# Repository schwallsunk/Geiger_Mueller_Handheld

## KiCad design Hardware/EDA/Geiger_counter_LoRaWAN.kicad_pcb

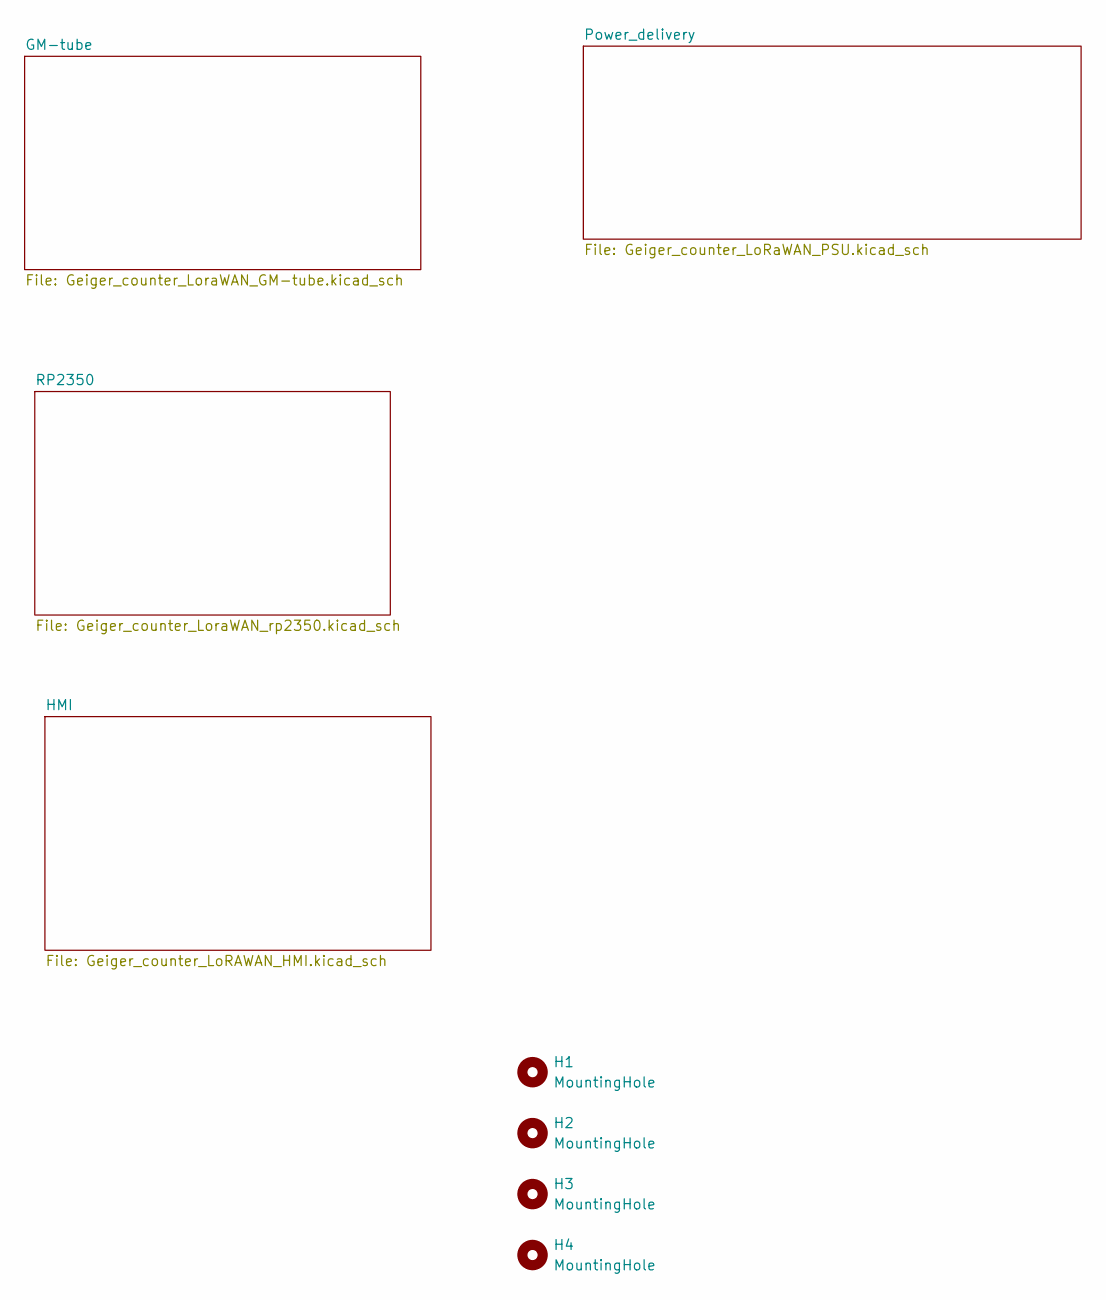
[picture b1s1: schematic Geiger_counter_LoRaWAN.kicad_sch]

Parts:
H1, H2, H3, H4: MountingHole; MountingHole_3.2mm_M3_ISO14580

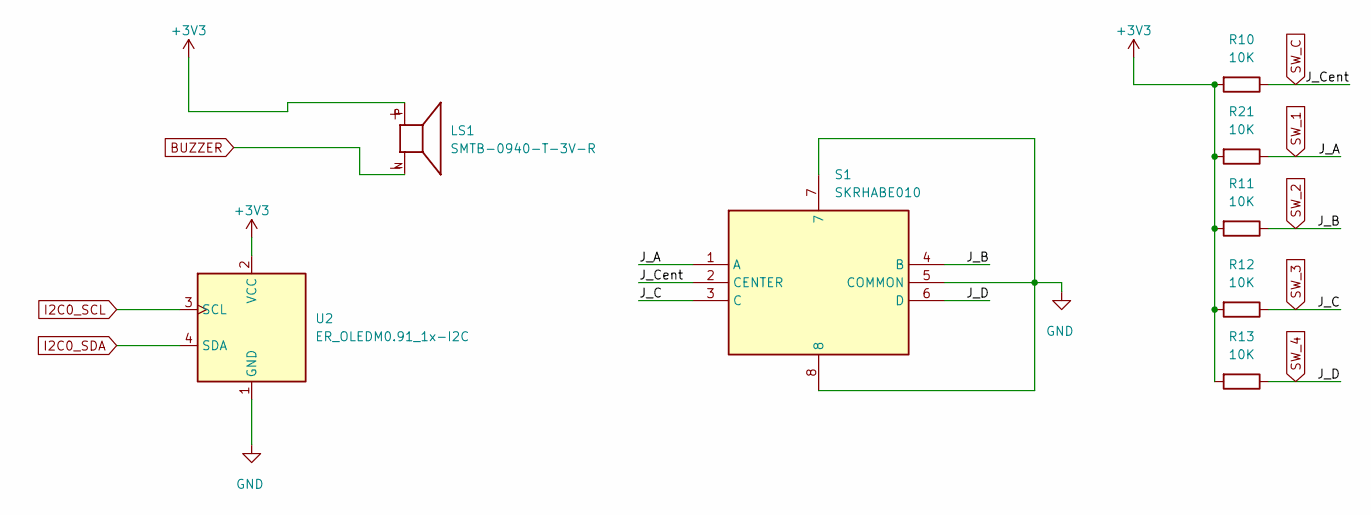
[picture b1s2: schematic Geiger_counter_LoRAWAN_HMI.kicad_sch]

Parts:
LS1: SMTB-0940-T-3V-R; XDCR_SMTB-0940-T-3V-R; PARTREV 01/24/2017
R10, R11, R12, R13, R21: 10K; R_0402_1005Metric
S1: SKRHABE010; Manufacturer_Part_Number SKRHABE010; Mouser Part Number 688-SKRHAB
U2: ER_OLEDM0.91_1x-I2C

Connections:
+3V3: LS1.P, R10.2, R11.2, R12.2, R13.2, R21.2, U2.2 (VCC); also elsewhere on the board
BUZZER: LS1.N; also elsewhere on the board
GND: S1.5 (COMMON), S1.7, S1.8, U2.1 (GND); also elsewhere on the board
I2C0_SCL: U2.3 (SCL); also elsewhere on the board
I2C0_SDA: U2.4 (SDA); also elsewhere on the board
SW_1: R21.1, S1.1 (A); also elsewhere on the board
SW_2: R11.1, S1.4 (B); also elsewhere on the board
SW_3: R12.1, S1.3 (C); also elsewhere on the board
SW_4: R13.1, S1.6 (D); also elsewhere on the board
SW_C: R10.1, S1.2 (CENTER); also elsewhere on the board

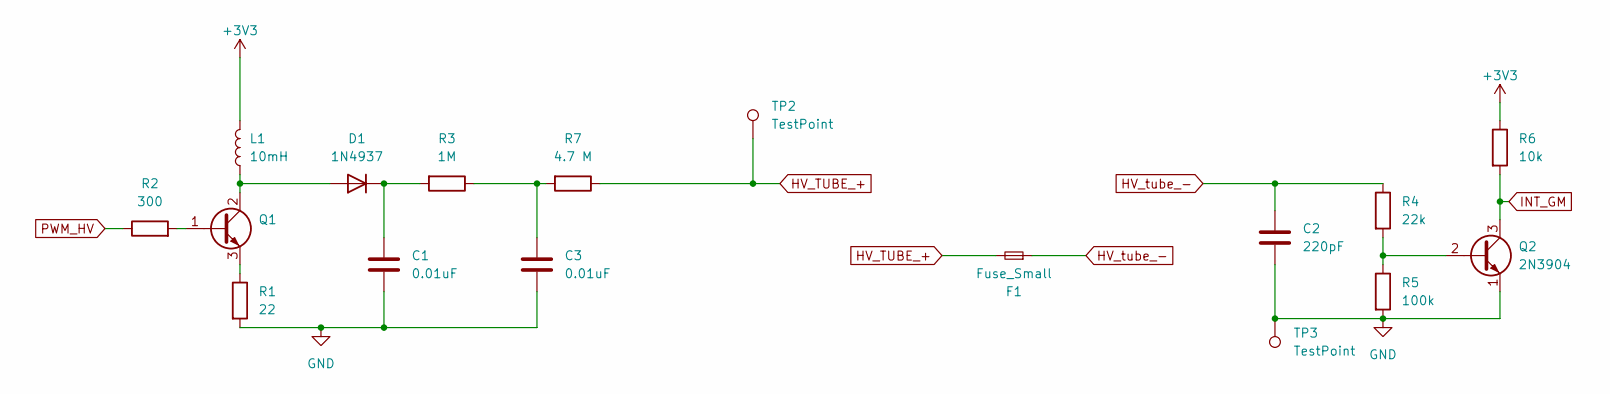
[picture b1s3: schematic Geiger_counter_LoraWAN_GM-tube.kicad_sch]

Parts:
C1, C3: 0.01uF; C_Rect_L11.0mm_W6.3mm_P10.00mm_MKT
C2: 220pF; C_Rect_L16.5mm_W7.3mm_P15.00mm_MKT
D1: 1N4937; D_DO-41_SOD81_P10.16mm_Horizontal
F1: Fuse_Small; SBM-20_GM_holder
L1: 10mH; L_Radial_D9.5mm_P5.00mm_Fastron_07HVP
Q1: MJE13003; TO-92_Inline_Wide
Q2: 2N3904; TO-92_Inline_Wide
R1: 22; R_Axial_DIN0516_L15.5mm_D5.0mm_P20.32mm_Horizontal
R2: 300; R_Axial_DIN0207_L6.3mm_D2.5mm_P10.16mm_Horizontal
R3: 1M; R_Axial_DIN0411_L9.9mm_D3.6mm_P15.24mm_Horizontal
R4: 22k; R_Axial_DIN0516_L15.5mm_D5.0mm_P20.32mm_Horizontal
R5: 100k; R_Axial_DIN0414_L11.9mm_D4.5mm_P20.32mm_Horizontal
R6: 10k; R_Axial_DIN0309_L9.0mm_D3.2mm_P15.24mm_Horizontal
R7: 4.7 M; R_Axial_DIN0411_L9.9mm_D3.6mm_P15.24mm_Horizontal
TP2, TP3: TestPoint; TestPoint_Loop_D2.50mm_Drill1.0mm

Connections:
+3V3: L1.2, R6.1; also elsewhere on the board
GND: C1.2, C2.2, C3.2, Q2.1 (E), R1.2, R5.2, TP3.1 (1_1); also elsewhere on the board
HV_TUBE_+: F1.2, R7.1, TP2.1 (1_1)
HV_tube_-: C2.1, F1.1, R4.1
INT_GM: Q2.3 (C), R6.2; also elsewhere on the board
unnamed: C3.1, R3.1, R7.2
unnamed: D1.2 (A), L1.1, Q1.2 (C)
unnamed: C1.1, D1.1 (K), R3.2
unnamed: Q1.1 (B), R2.2
unnamed: Q1.3 (E), R1.1
unnamed: Q2.2 (B), R4.2, R5.1
PWM_HV: R2.1; also elsewhere on the board

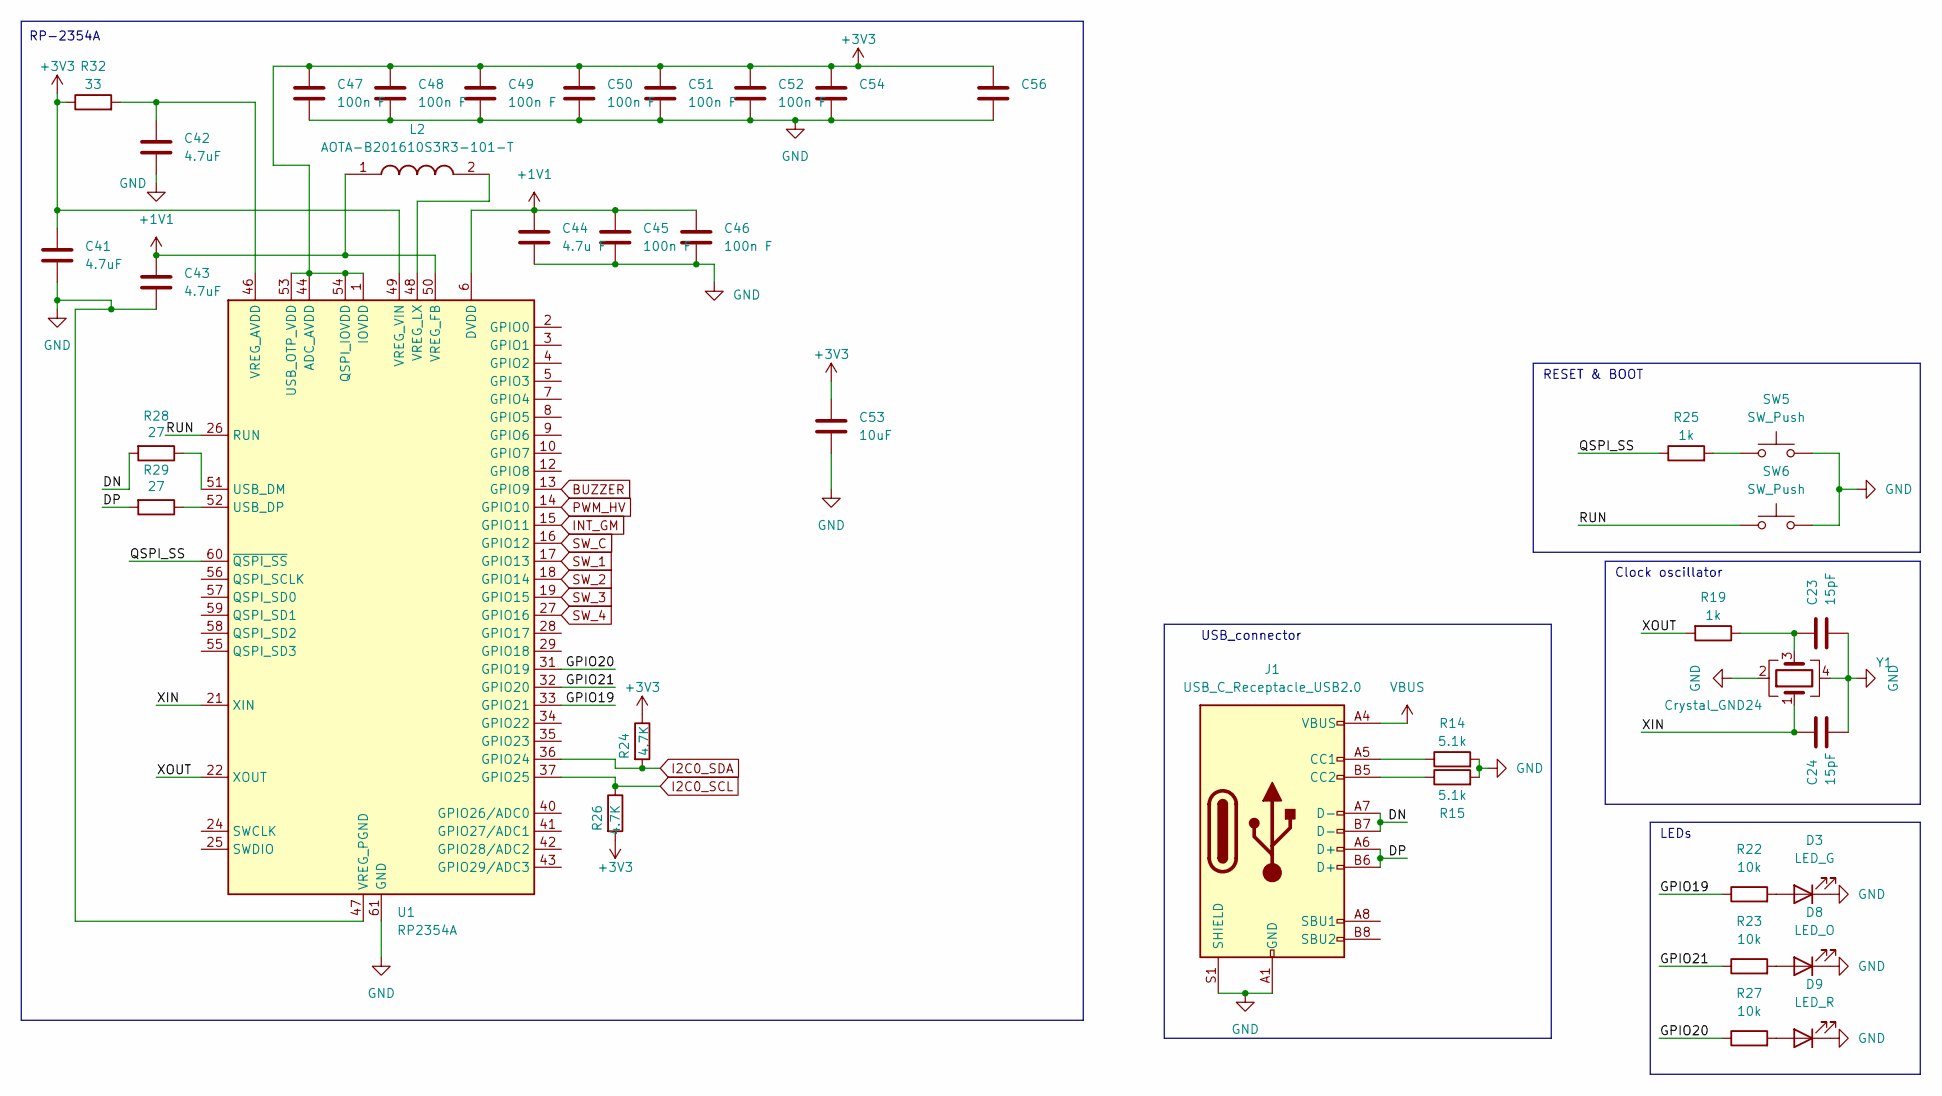
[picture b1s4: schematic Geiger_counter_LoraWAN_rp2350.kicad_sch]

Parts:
C23, C24: 15pF; C_0402_1005Metric_Pad0.74x0.62mm_HandSolder
C41, C42, C43: 4.7uF; C_0402_1005Metric
C44: 4.7u F; C_0402_1005Metric
C45, C46, C47, C48, C49, C50, C51, C52, C54, C56: 100n F; C_0201_0603Metric
C53: 10uF; C_0603_1608Metric
D3: LED_G; LED_0603_1608Metric_Pad1.05x0.95mm_HandSolder
D8: LED_O; LED_0603_1608Metric_Pad1.05x0.95mm_HandSolder
D9: LED_R; LED_0603_1608Metric_Pad1.05x0.95mm_HandSolder
J1: USB_C_Receptacle_USB2.0; USB_C_Receptacle_G-Switch_GT-USB-7010ASV
L2: AOTA-B201610S3R3-101-T; AOTAB201610S3R3101T; Manufacturer_Part_Number AOTA-B201610S3R3-101-T; Mouser Part Number 815-AB201610S3R3101T
R14, R15: 5.1k; R_0402_1005Metric_Pad0.72x0.64mm_HandSolder
R19, R25: 1k; R_0402_1005Metric_Pad0.72x0.64mm_HandSolder
R22, R23, R27: 10k; R_0402_1005Metric
R24, R26: 4.7K; R_0402_1005Metric_Pad0.72x0.64mm_HandSolder
R28, R29: 27; R_0402_1005Metric
R32: 33; R_0402_1005Metric_Pad0.72x0.64mm_HandSolder
SW5, SW6: SW_Push; SW_SPST_CK_RS282G05A3
U1: RP2354A; QFN-60-1EP_7x7mm_P0.4mm_EP3.4x3.4mm
Y1: Crystal_GND24; Crystal_SMD_3225-4Pin_3.2x2.5mm

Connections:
+1V1: C43.1, C44.1, C45.1, C46.1, L2.1, U1.6 (DVDD), U1.23 (DVDD), U1.39 (DVDD), U1.50 (VREG_FB)
+3V3: C41.1, C47.1, C48.1, C49.1, C50.1, C51.1, C52.1, C53.2, C54.1, C56.1, R24.1, R26.2, R32.1, U1.1 (IOVDD), U1.11 (IOVDD), U1.20 (IOVDD), U1.30 (IOVDD), U1.38 (IOVDD), U1.44 (ADC_AVDD), U1.45 (IOVDD), U1.49 (VREG_VIN), U1.53 (USB_OTP_VDD), U1.54 (QSPI_IOVDD); also elsewhere on the board
/RP2350/DN: J1.A7 (D-), J1.B7 (D-), R28.2
/RP2350/DP: J1.A6 (D+), J1.B6 (D+), R29.2
/RP2350/GPIO19: R22.1, U1.33 (GPIO21)
/RP2350/GPIO20: R27.1, U1.31 (GPIO19)
/RP2350/GPIO21: R23.1, U1.32 (GPIO20)
/RP2350/QSPI_SS: R25.1, U1.60 (~QSPI_SS)
/RP2350/RUN: SW6.1, U1.26 (RUN)
/RP2350/XIN: C24.1, U1.21 (XIN), Y1.1
/RP2350/XOUT: R19.2, U1.22 (XOUT)
BUZZER: U1.13 (GPIO9); also elsewhere on the board
GND: C23.2, C24.2, C41.2, C42.2, C43.2, C44.2, C45.2, C46.2, C47.2, C48.2, C49.2, C50.2, C51.2, C52.2, C53.1, C54.2, C56.2, D3.1 (K), D8.1 (K), D9.1 (K), J1.A1 (GND), J1.A12 (GND), J1.B1 (GND), J1.B12 (GND), J1.S1 (SHIELD), R14.2, R15.2, SW5.2, SW6.2, U1.47 (VREG_PGND), U1.61 (GND), Y1.2, Y1.4; also elsewhere on the board
I2C0_SCL: R26.1, U1.37 (GPIO25); also elsewhere on the board
I2C0_SDA: R24.2, U1.36 (GPIO24); also elsewhere on the board
INT_GM: U1.15 (GPIO11); also elsewhere on the board
unnamed: C23.1, R19.1, Y1.3
unnamed: D3.2 (A), R22.2
unnamed: D8.2 (A), R23.2
unnamed: D9.2 (A), R27.2
unnamed: J1.A5 (CC1), R14.1
unnamed: J1.B5 (CC2), R15.1
unnamed: R25.2, SW5.1
unnamed: R28.1, U1.51 (USB_DM)
unnamed: R29.1, U1.52 (USB_DP)
unnamed: C42.1, R32.2, U1.46 (VREG_AVDD)
unnamed: L2.2, U1.48 (VREG_LX)
PWM_HV: U1.14 (GPIO10); also elsewhere on the board
SW_1: U1.17 (GPIO13); also elsewhere on the board
SW_2: U1.18 (GPIO14); also elsewhere on the board
SW_3: U1.19 (GPIO15); also elsewhere on the board
SW_4: U1.27 (GPIO16); also elsewhere on the board
SW_C: U1.16 (GPIO12); also elsewhere on the board
VBUS: J1.A4 (VBUS), J1.A9 (VBUS), J1.B4 (VBUS), J1.B9 (VBUS); also elsewhere on the board

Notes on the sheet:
Clock oscillator
RESET & BOOT
RP-2354A
USB_connector
LEDs

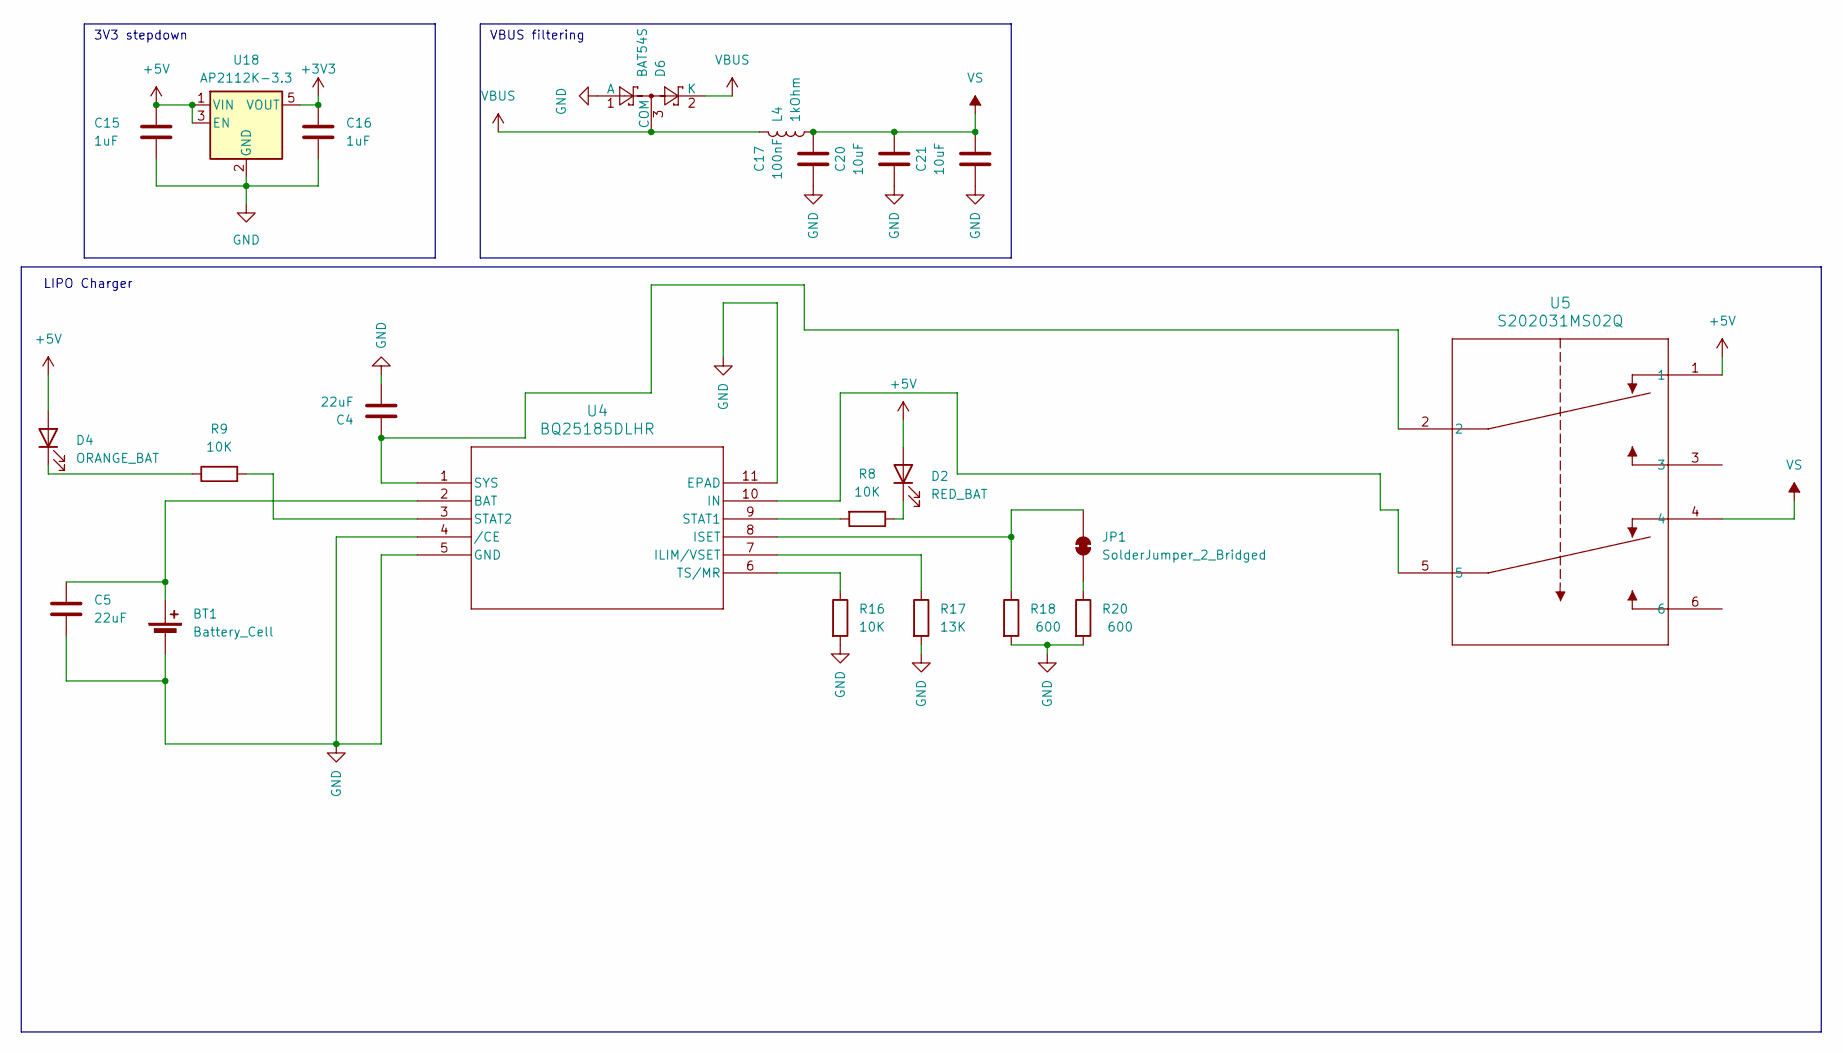
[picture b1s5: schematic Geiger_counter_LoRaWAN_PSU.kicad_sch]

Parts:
BT1: Battery_Cell; BatteryHolder_Keystone_1042_1x18650
C4: 22uF; C_0603_1608Metric
C5: 22uF; C_0402_1005Metric
C15, C16: 1uF; C_0603_1608Metric_Pad1.08x0.95mm_HandSolder
C17: 100nF; R_0603_1608Metric_Pad0.98x0.95mm_HandSolder
C20, C21: 10uF; C_1206_3216Metric_Pad1.33x1.80mm_HandSolder
D2: RED_BAT; LED_0603_1608Metric_Pad1.05x0.95mm_HandSolder
D4: ORANGE_BAT; LED_0603_1608Metric_Pad1.05x0.95mm_HandSolder
D6: BAT54S; SOT-23
JP1: SolderJumper_2_Bridged; SolderJumper-2_P1.3mm_Open_Pad1.0x1.5mm
L4: 1kOhm; R_0603_1608Metric_Pad0.98x0.95mm_HandSolder
R8, R9, R16: 10K; R_0402_1005Metric
R17: 13K; R_0402_1005Metric
R18, R20: 600; R_0402_1005Metric
U4: BQ25185DLHR; WSON10_DLH_TEX-M
U5: S202031MS02Q; SWITCH_S20203
U18: AP2112K-3.3; SOT-23-5

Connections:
+3V3: C16.1, U18.5 (VOUT); also elsewhere on the board
+5V: C15.1, D2.2 (A), D4.2 (A), U5.1, U18.1 (VIN), U18.3 (EN)
GND: BT1.2 (-), C4.2, C5.2, C15.2, C16.2, C17.2, C20.2, C21.1, D6.1 (A), R16.2, R17.2, R18.2, R20.2, U4.4 (/CE), U4.5 (GND), U4.11 (EPAD), U18.2 (GND); also elsewhere on the board
unnamed: BT1.1 (+), C5.1, U4.2 (BAT)
unnamed: D2.1 (K), R8.1
unnamed: D4.1 (K), R9.1
unnamed: JP1.1 (A), R20.1
unnamed: JP1.2 (B), R18.1, U4.8 (ISET)
unnamed: R17.1, U4.7 (ILIM/VSET)
unnamed: U4.10 (IN), U5.5
unnamed: R8.2, U4.9 (STAT1)
unnamed: R9.2, U4.3 (STAT2)
unnamed: C4.1, U4.1 (SYS), U5.2
unnamed: R16.1, U4.6 (TS/MR)
VBUS: D6.2 (K), D6.3 (COM), L4.2; also elsewhere on the board
VS: C17.1, C20.1, C21.2, L4.1, U5.4

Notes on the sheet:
LIPO Charger
VBUS filtering
3V3 stepdown

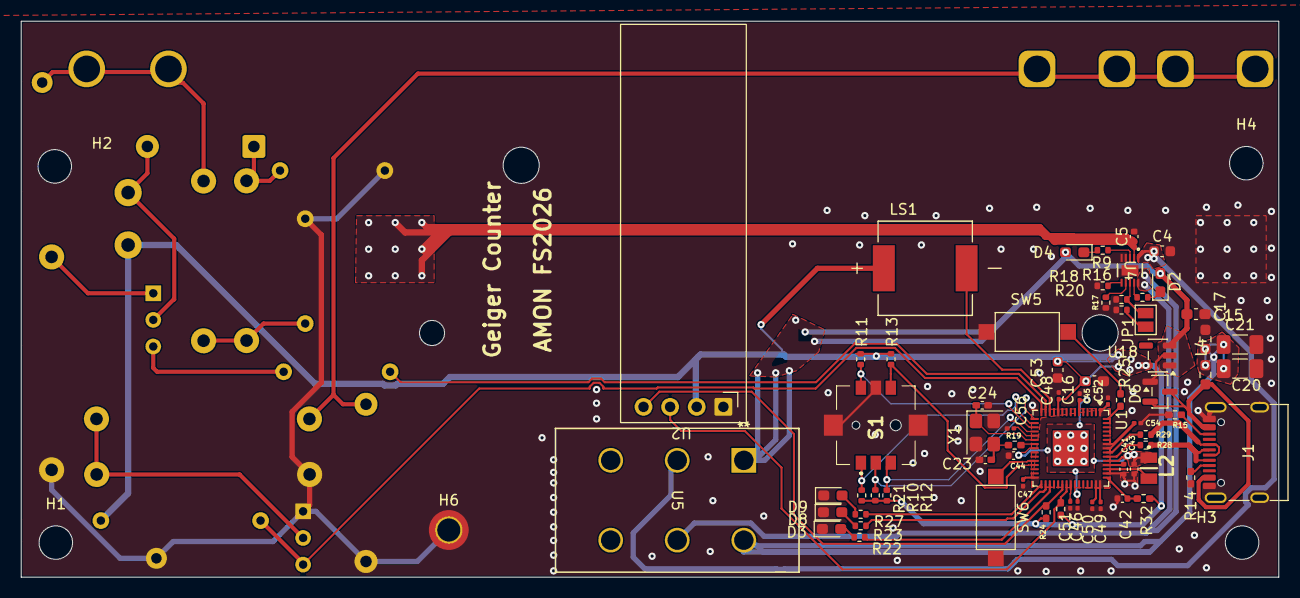
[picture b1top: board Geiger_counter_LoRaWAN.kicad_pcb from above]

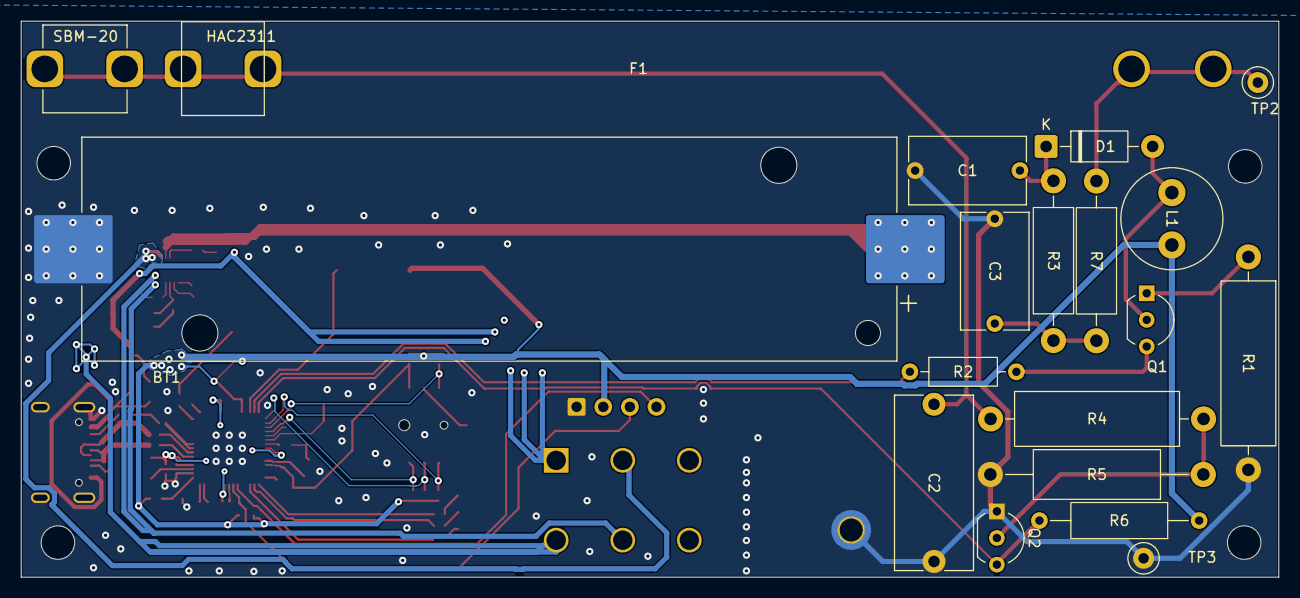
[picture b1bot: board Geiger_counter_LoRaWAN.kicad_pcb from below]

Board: 2 copper layers, 120.0 x 53.0 mm, 90 parts (18 on the bottom side), 55 nets.

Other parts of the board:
H6: MountingHole_Pad; MountingHole_2.2mm_M2_DIN965_Pad_TopBottom

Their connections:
GND: H6.1 (1_1); also elsewhere on the board
